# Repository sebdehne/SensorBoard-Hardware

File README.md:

# RoomSensorV2-Hardware
KiCad design files for my RoomSensorV2 - a battery power, wireless, environment sensor 

- [Temperature, humidity](https://www.amphenol-sensors.com/en/telaire/humidity/527-humidity-sensors/3095-chipcap-2) and light sensor
- ARM® Cortex®-M0+ based atsamd21g18a microcontroller (way overkill of course, but easier to program than a tiny 8-bit micro)
- [RN2483](https://www.microchip.com/wwwproducts/en/RN2483) LoRa wireless module
- Uses external RTC [DS3231SN#](https://no.mouser.com/ProductDetail/Maxim-Integrated/DS3231SN?qs=1eQvB6Dk1vhUlr8%2FOrV0Fw%3D%3D) to cut power to all components to achieve ~0.9µA sleep current
- USB-C for easy firmware updates - which are not really needed because I am going to implement over-the-air firmware updates

See [Schematic](images/schematic.pdf) and [3d-view](images/3d-view.png).

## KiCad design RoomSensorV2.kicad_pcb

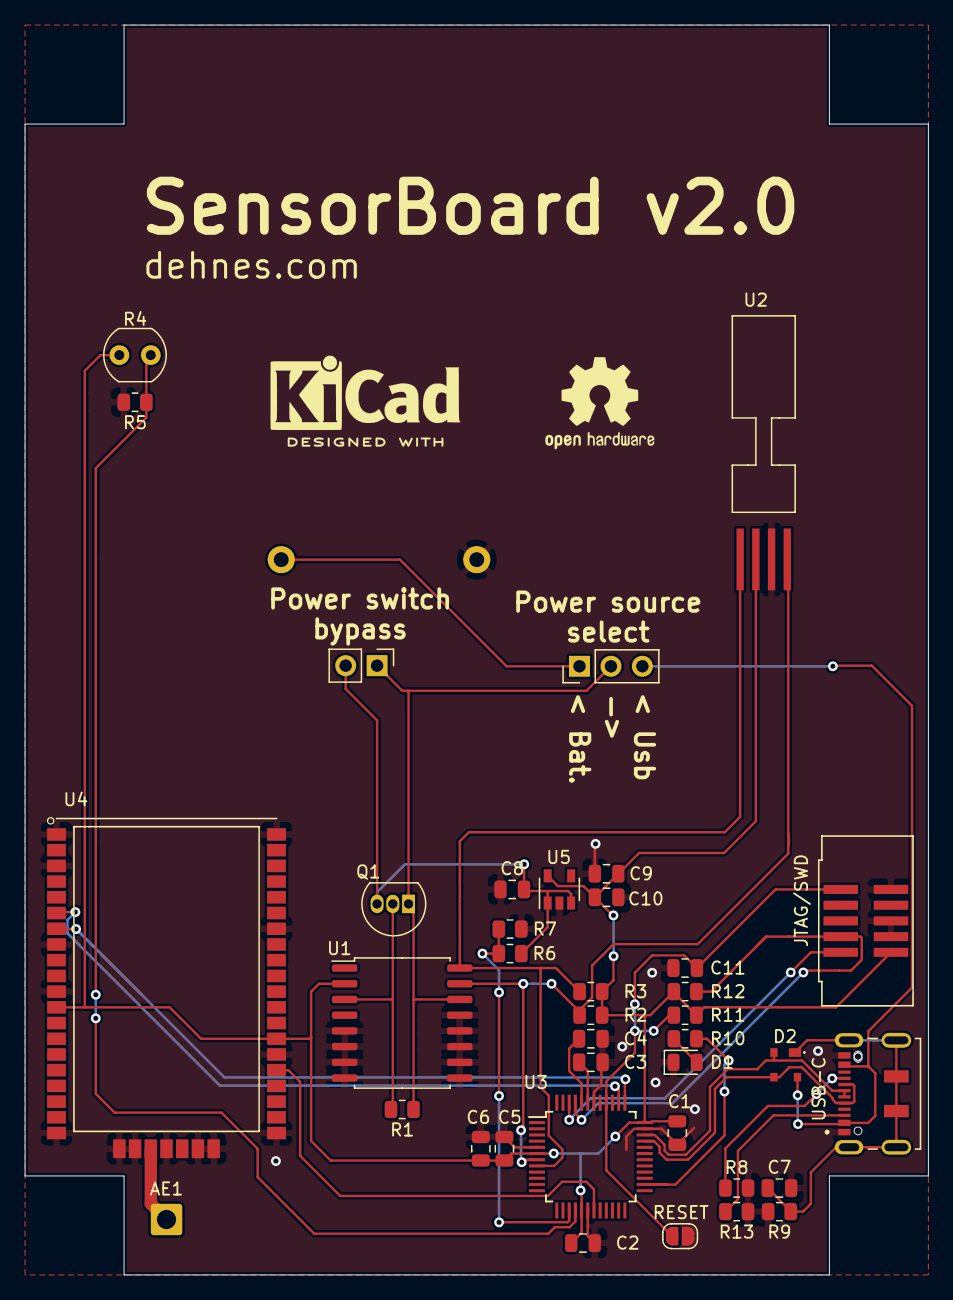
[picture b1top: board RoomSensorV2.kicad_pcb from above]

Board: 2 copper layers, 73.0 x 101.0 mm, 39 parts (1 on the bottom side), 27 nets.

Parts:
AE1: Antenna; SolderWire-0.75sqmm_1x01_D1.25mm_OD2.3mm
BT1: 3xAA 3.3-4.5V; Battery_holder_3xAA
C1, C2, C4, C5, C11: 100n; C_0805_2012Metric
C3, C10: 1uF; C_0805_2012Metric
C6: 4u7; C_0805_2012Metric
C7: 4n7; C_0805_2012Metric
C8, C9: 10uF; C_0805_2012Metric
D1: LED BLUE APTD2012LQBC/D; LED_0805_2012Metric
D2: PRTR5V0U2X,215; SOT143B
J1: Conn_01x03; PinHeader_1x03_P2.54mm_Vertical
J2: Conn_01x02; PinHeader_1x02_P2.54mm_Vertical
JTAG/SWD: SHF-105-01-F-D-SM; SHF-105-01-X-D-SM
Q1: TP0606N3-G; TO-92L_Inline
R1, R6, R7: 10k; R_0805_2012Metric
R2, R3: 4k7; R_0805_2012Metric
R4: R_PHOTO; R_LDR_4.9x4.2mm_P2.54mm_Vertical
R5: 10k / 100k; R_0805_2012Metric
R8, R13: 5k1; R_0805_2012Metric
R9: 1M; R_0805_2012Metric
R10: 300R; R_0805_2012Metric
R11: 100k; R_0805_2012Metric
R12: 1k; R_0805_2012Metric
RESET: TestPoint_2Pole; SolderJumper-2_P1.3mm_Open_RoundedPad1.0x1.5mm
U1: DS3231SN#; SOIC-16W_7.5x10.3mm_P1.27mm
U2: ChipCap2-SIP; ChipCap2SIP
U3: ATSAMD21G18A-A; TQFP-48_7x7mm_P0.5mm
U4: RN2483-I_RM095; RM095
U5: TC1186; SOT-23-5
USB-C: DX07S016JA1R1500; JAE_DX07S016JA1R1500

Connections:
3V3: C1.1, C2.1, C5.1, C6.1, C9.2, C10.2, JTAG/SWD.1, R2.1, R3.1, R4.1, R11.1, R12.1, U1.2, U2.2, U3.6, U3.17, U3.36, U4.12, U4.34, U5.5
GND: BT1.2, C1.2, C2.2, C3.2, C4.2, C5.2, C6.2, C7.2, C8.1, C9.1, C10.1, C11.2, D1.1, JTAG/SWD.3, JTAG/SWD.5, JTAG/SWD.9, R5.2, R7.2, R8.2, R9.2, R13.1, RESET.2, U1.5, U1.6, U1.7, U1.8, U1.9, U1.10, U1.11, U1.12, U1.13, U2.3, U3.5, U3.18, U3.35, U3.42, U4.1, U4.3, U4.8, U4.11, U4.20, U4.21, U4.22, U4.24, U4.26, U4.27, U4.28, U4.33, U4.41, U4.47, U5.2, USB-C.1, USB-C.12
I2C_SCL: R3.2, U1.16, U2.1, U3.8
I2C_SDA: R2.2, U1.15, U2.4, U3.7
LIGHT_READ: R4.2, R5.1, U3.16
unnamed: AE1.1, U4.23
unnamed: C3.1, U3.43
unnamed: C4.1, U3.44
unnamed: C7.1, D2.1, R9.1, USB-C.S1, USB-C.S2, USB-C.S3, USB-C.S4, USB-C.S5, USB-C.S6
unnamed: D1.2, R10.2
unnamed: D2.2, U3.34, USB-C.6, USB-C.7
unnamed: D2.3, U3.33, USB-C.5, USB-C.8
unnamed: R13.2, USB-C.3
unnamed: R8.1, USB-C.9
unnamed: Q1.2, R1.2, U1.3
unnamed: R10.1, U3.26
RESET: C11.1, JTAG/SWD.10, R11.2, RESET.1, U3.40
RN2483_RESET: U3.19, U4.32
RN2483_UART_RX: U3.37, U4.7
RN2483_UART_TX: U3.38, U4.6
SWDCLK: JTAG/SWD.4, R12.2, U3.45
SWDIO: JTAG/SWD.2, U3.46
VSwitched: C8.2, J2.2, Q1.3, R6.1, U5.1, U5.3
VUSB: D2.4, J1.3, USB-C.2, USB-C.11
V_Bat: BT1.1, J1.1
V_Bat_READ: R6.2, R7.1, U3.15
V_Source: J1.2, J2.1, Q1.1, R1.1, U1.14

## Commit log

2021-03-28 added PCB
2021-04-11 Replaced Seeeduino XIAO by using ATSAMD21G18A microcontroller directly
2021-04-14 Revision 1.0
2021-05-02 added datasheet link
